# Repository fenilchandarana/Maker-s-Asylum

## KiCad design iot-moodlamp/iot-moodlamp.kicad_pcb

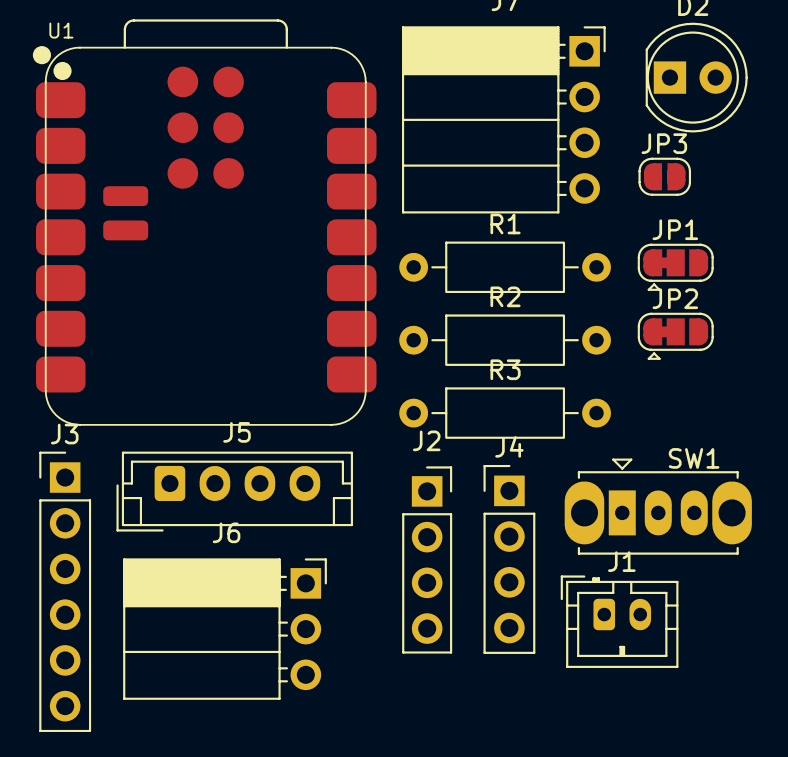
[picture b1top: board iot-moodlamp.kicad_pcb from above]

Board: 2 copper layers, 16 parts (0 on the bottom side), 19 nets, no tracks yet.

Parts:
D2: LED; LED_D5.0mm
J1: battery; JST_PH_B2B-PH-K_1x02_P2.00mm_Vertical
J2: i2c; PinSocket_1x04_P2.54mm_Vertical
J3: spi; PinHeader_1x06_P2.54mm_Vertical
J4: WS2812B; PinHeader_1x04_P2.54mm_Vertical
J5: WS2812B; JST_EH_B4B-EH-A_1x04_P2.50mm_Vertical
J6: dht11 module; PinSocket_1x03_P2.54mm_Horizontal
J7: mq module; PinSocket_1x04_P2.54mm_Horizontal
JP1: vcc-gnd; SolderJumper-3_P1.3mm_Bridged12_RoundedPad1.0x1.5mm
JP2: gnd-vcc; SolderJumper-3_P1.3mm_Bridged12_RoundedPad1.0x1.5mm
JP3: Jumper_2_Open; SolderJumper-2_P1.3mm_Open_RoundedPad1.0x1.5mm
R1: 10k; R_Axial_DIN0207_L6.3mm_D2.5mm_P10.16mm_Horizontal
R2: 4.7k; R_Axial_DIN0207_L6.3mm_D2.5mm_P10.16mm_Horizontal
R3: 220o; R_Axial_DIN0207_L6.3mm_D2.5mm_P10.16mm_Horizontal
SW1: SW_SPDT; SW_Slide_SPDT_Straight_CK_OS102011MS2Q
U1: XIAO ESP32C3; XIAO-ESP32C3-SMD

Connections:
+3V3: J3.1, J6.1, JP1.1 (A), JP2.3 (B), JP3.1 (A), U1.12 (VCC_3V3)
+5V: J4.2, J5.2, J7.1, U1.14 (VUSB)
/bat+: R1.1, SW1.3 (C), U1.15 (Batt+)
GND: D2.1 (K), J1.2, J3.2, J4.3, J5.3, J6.3, J7.2, JP1.3 (B), JP2.1 (A), R2.2, U1.13 (GND), U1.16 (Batt-)
unnamed: D2.2 (A), R3.2
unnamed: J1.1, SW1.2 (B)
unnamed: J2.1, JP1.2 (C)
unnamed: J2.2, JP2.2 (C)
unnamed: J2.3, U1.6 (D5)
unnamed: J2.4, U1.5 (D4)
unnamed: J3.3, U1.10 (D9)
unnamed: J3.4, U1.11 (D10)
unnamed: J3.5, U1.9 (D8)
unnamed: J3.6, U1.8 (D7)
unnamed: J4.1, J5.1, U1.3 (D2)
unnamed: J6.2, U1.1 (D0)
unnamed: J7.4, U1.2 (D1)
unnamed: JP3.2 (B), R3.1
unnamed: R1.2, R2.1, U1.4 (D3)

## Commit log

2025-05-28 esp32 benchmark for quality check added
2025-05-28 renamed the webserver to wifi
2025-05-28 renamed a file
2025-05-29 added the appscript for library and inventory google sheet
2025-05-31 program for may cohort 1 added
2025-06-06 updated scripts for inventory and library management system, for trial
2025-06-11 updated the scripts and added the xlsx sheet before the run
2025-06-13 credentials for esp_wifi_ringled
2025-06-24 codes for summer 2025 recidency added
2025-06-27 added arcade code, which checks all the components
2025-07-01 cohort 4 codes added
2025-07-03 cohort 4 image to text added
2025-07-08 cohort 5 code and arcade codes added
2025-07-09 servo for xiao esp32c6 added
2025-07-09 code for pH sensor added
2025-07-12 cohort 5 one handed keyboard code added
2025-07-12 hourglass animation logic added
2025-07-12 bug fixed for the fulanimation code
2025-07-21 ims folder updated after making 1st kit
2025-07-23 inventory & library sheet and appscripts added post production of 8 kits
2025-08-08 tested the v1 of inventory and IS Kit Library appscripts, looks good so far
2025-08-09 renamed the xlxs file and added updated sto file. Inventory and library v1
2025-08-16 visiting card collector code added
2025-08-21 haptic motor added for arcade
2025-10-16 iot moodlamp kicad files added
